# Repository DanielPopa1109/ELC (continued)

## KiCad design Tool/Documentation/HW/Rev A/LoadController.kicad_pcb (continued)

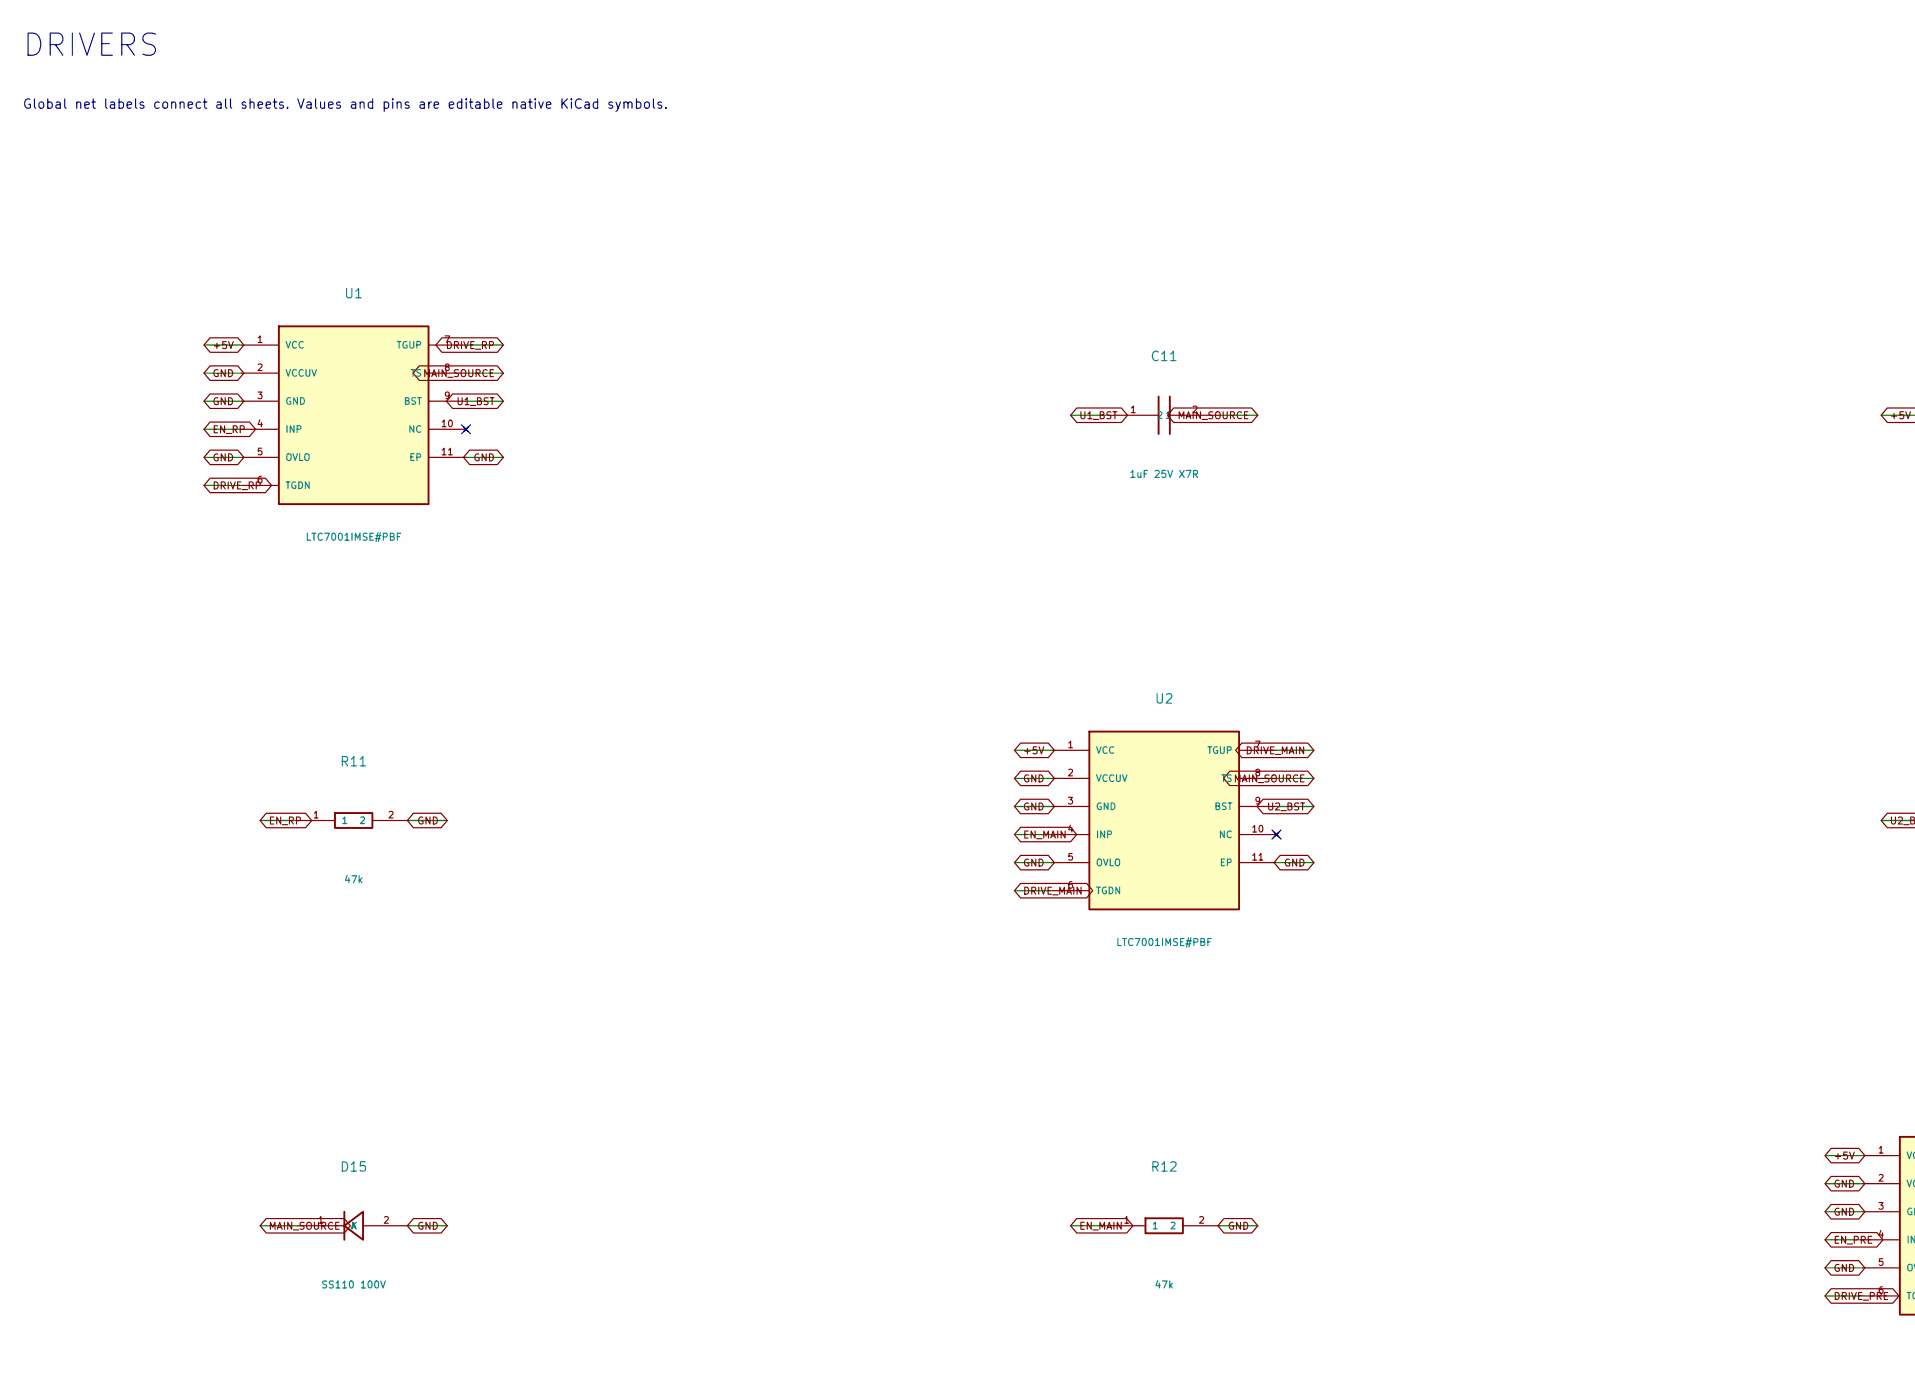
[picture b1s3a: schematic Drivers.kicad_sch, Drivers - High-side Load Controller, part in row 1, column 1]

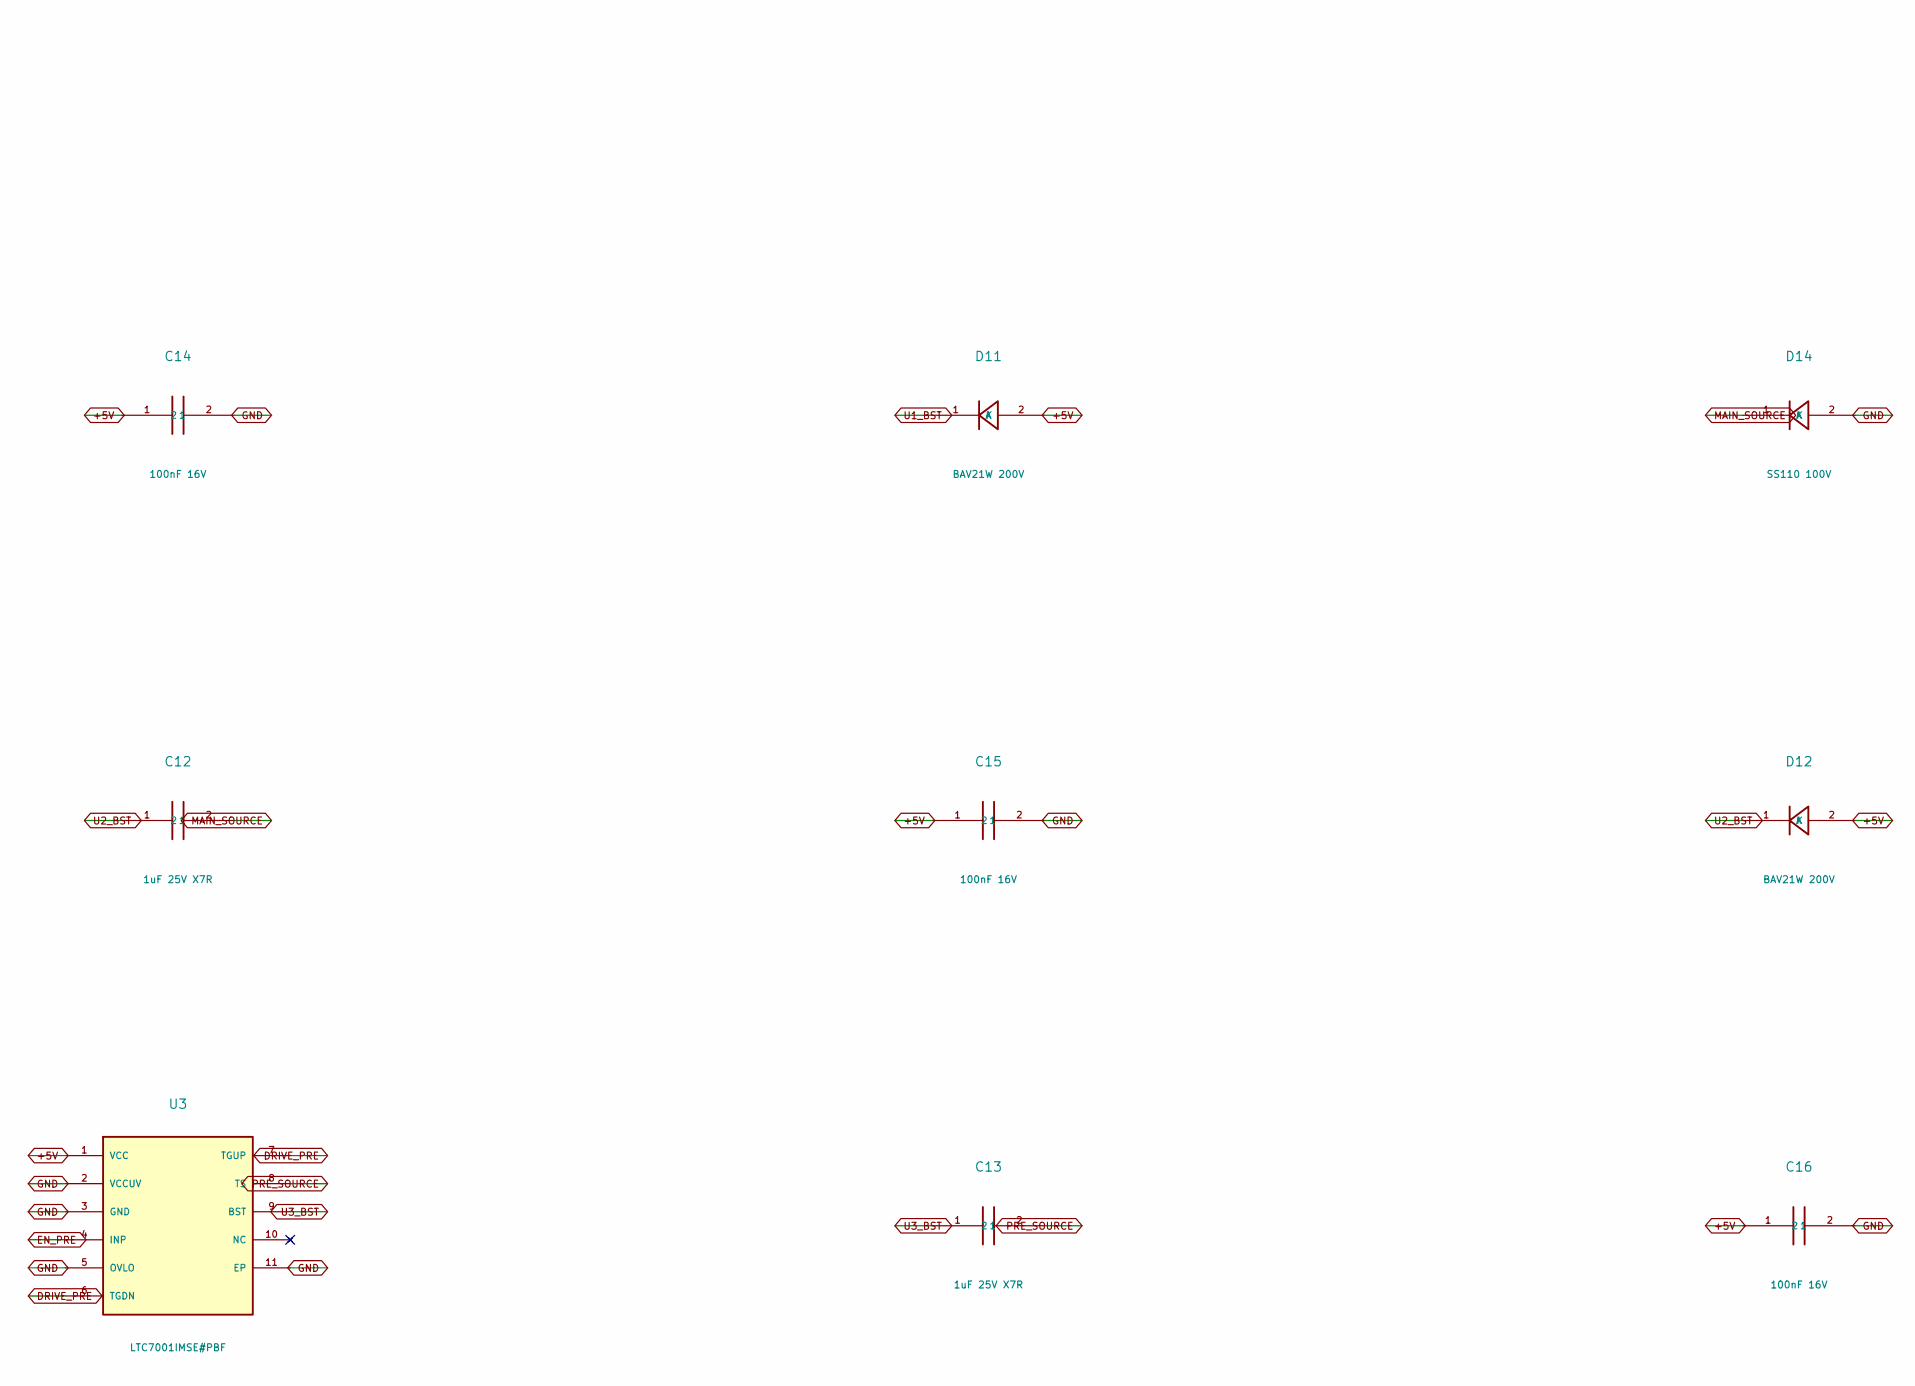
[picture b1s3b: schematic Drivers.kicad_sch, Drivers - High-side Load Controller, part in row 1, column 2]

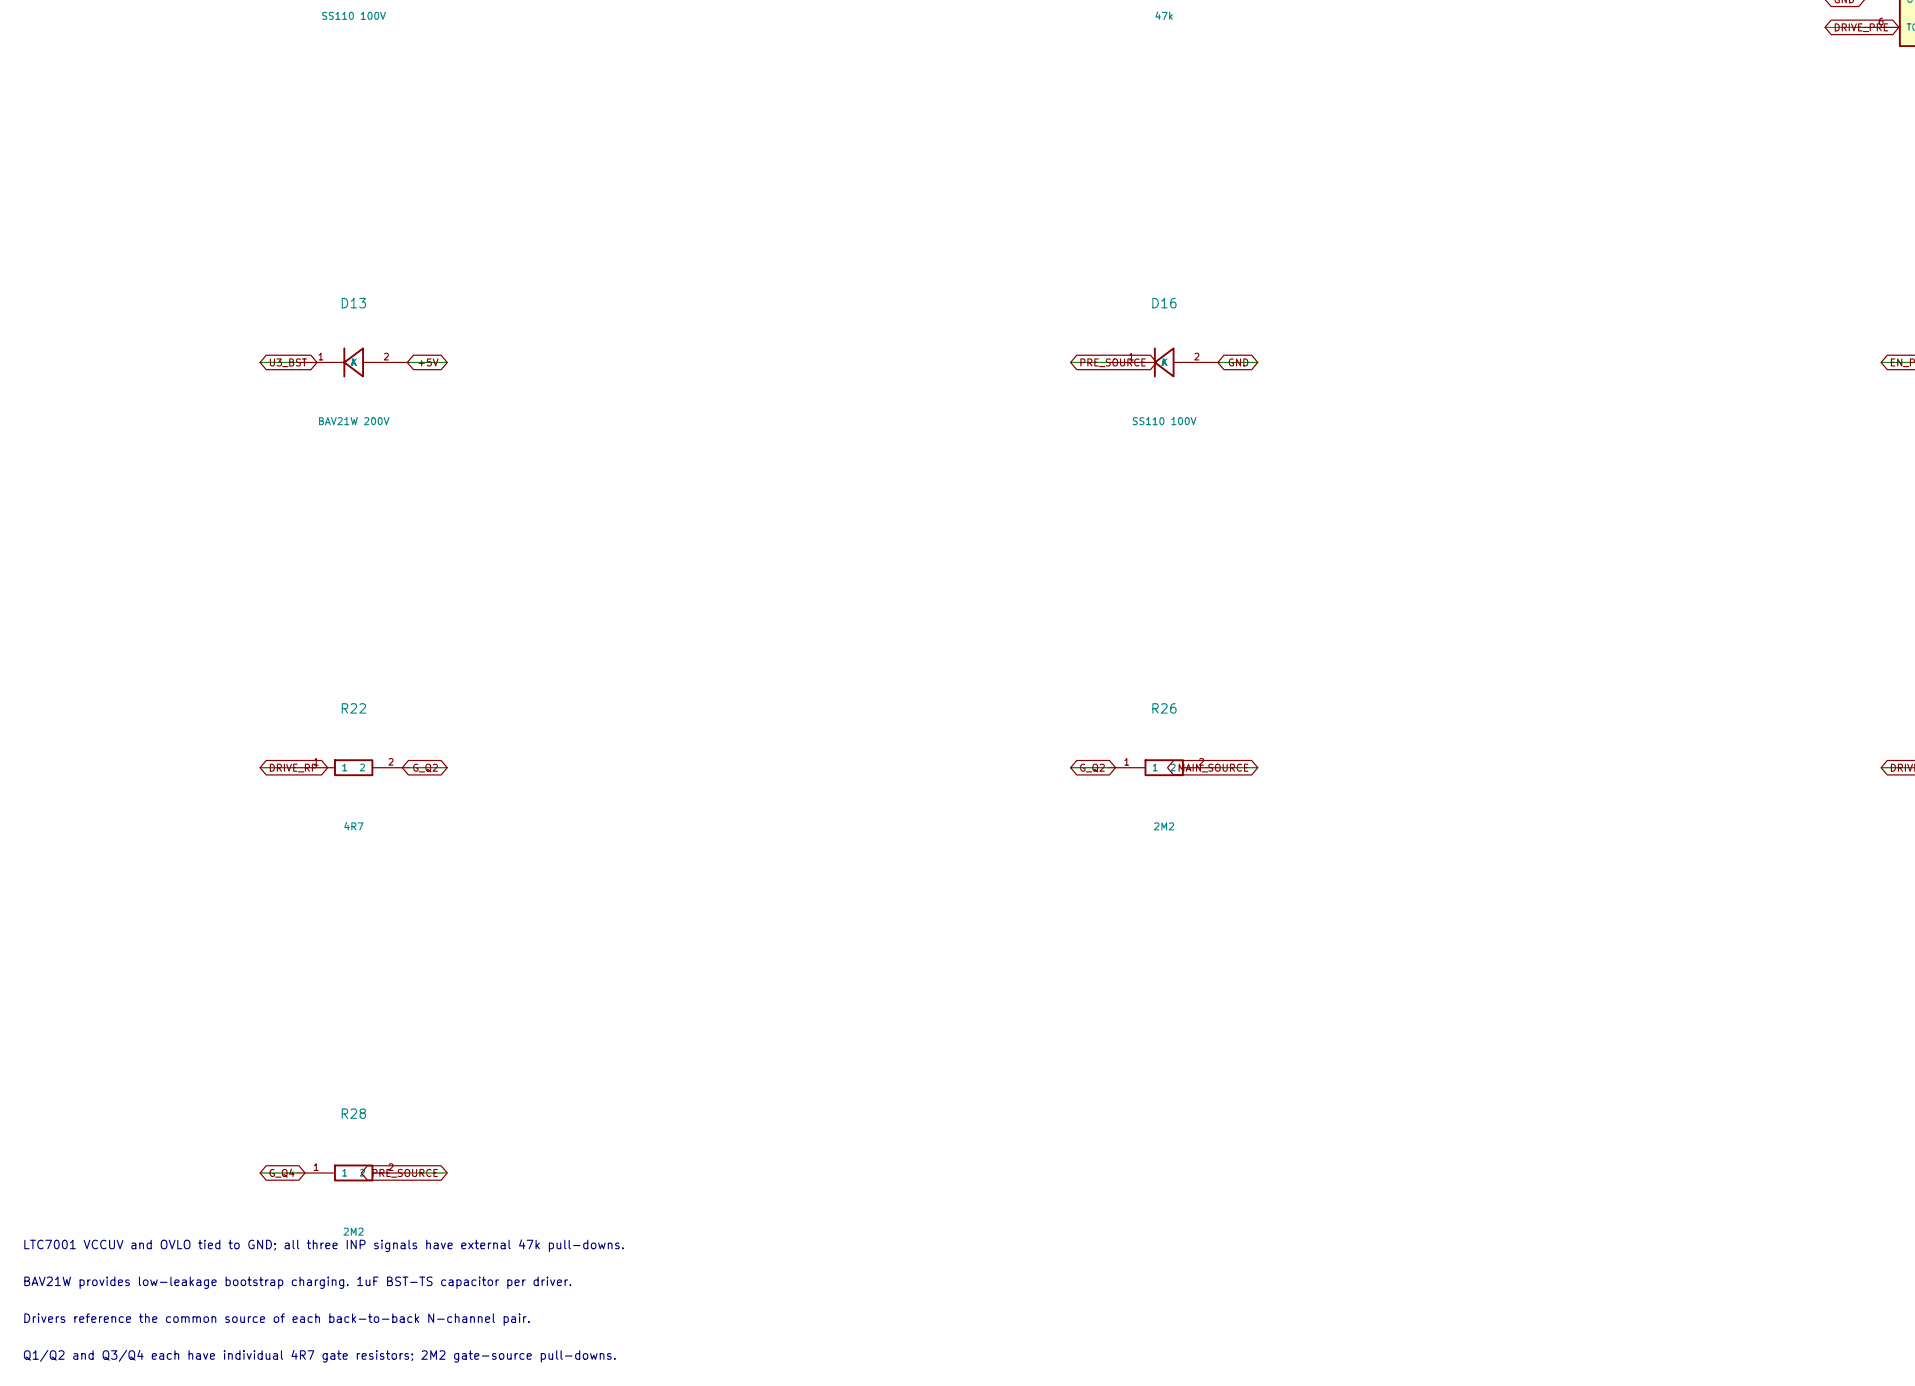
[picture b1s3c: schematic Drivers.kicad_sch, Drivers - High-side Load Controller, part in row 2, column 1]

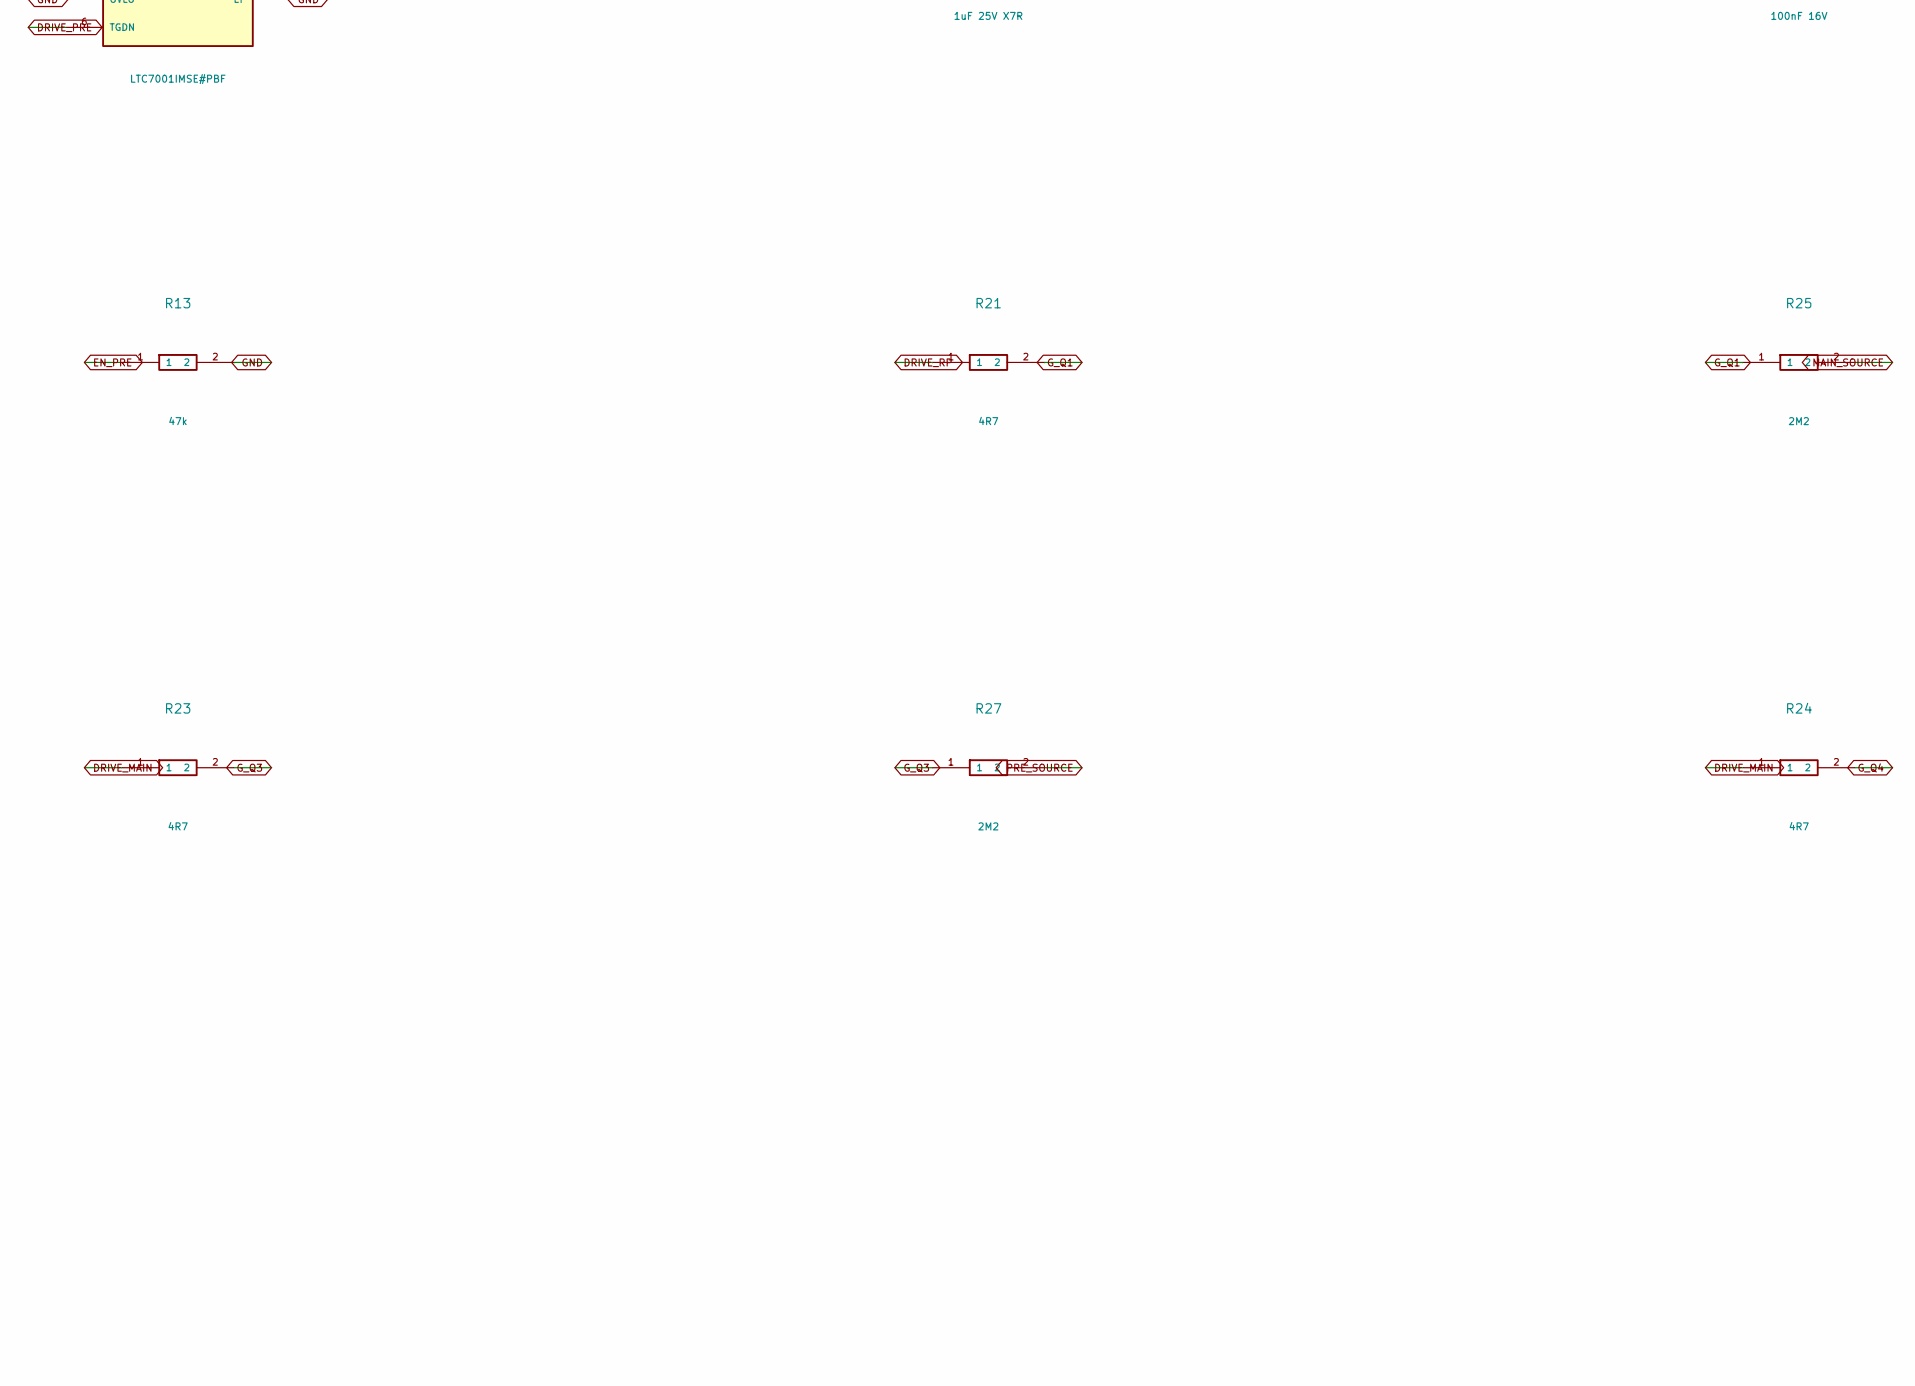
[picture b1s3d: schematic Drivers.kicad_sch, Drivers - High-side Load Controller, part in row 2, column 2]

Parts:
C11, C12, C13: 1uF 25V X7R; 0805
C14, C15, C16: 100nF 16V; 0805
D11, D12, D13: BAV21W 200V; SOD123
D14, D15, D16: SS110 100V; SMA
R11, R12, R13: 47k; 0805
R21, R22, R23, R24: 4R7; 0805
R25, R26, R27, R28: 2M2; 0805
U1, U2, U3: LTC7001IMSE#PBF; MSOP10_EP

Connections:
+5V: C14.1, C15.1, C16.1, D11.2 (A), D12.2 (A), D13.2 (A), U1.1 (VCC), U2.1 (VCC), U3.1 (VCC); also elsewhere on the board
DRIVE_MAIN: R23.1, R24.1, U2.6 (TGDN), U2.7 (TGUP)
DRIVE_PRE: U3.6 (TGDN), U3.7 (TGUP); also elsewhere on the board
DRIVE_RP: R21.1, R22.1, U1.6 (TGDN), U1.7 (TGUP)
EN_MAIN: R12.1, U2.4 (INP); also elsewhere on the board
EN_PRE: R13.1, U3.4 (INP); also elsewhere on the board
EN_RP: R11.1, U1.4 (INP); also elsewhere on the board
GND: C14.2, C15.2, C16.2, D14.2 (A), D15.2 (A), D16.2 (A), R11.2, R12.2, R13.2, U1.2 (VCCUV), U1.3 (GND), U1.5 (OVLO), U1.11 (EP), U2.2 (VCCUV), U2.3 (GND), U2.5 (OVLO), U2.11 (EP), U3.2 (VCCUV), U3.3 (GND), U3.5 (OVLO), U3.11 (EP); also elsewhere on the board
G_Q1: R21.2, R25.1; also elsewhere on the board
G_Q2: R22.2, R26.1; also elsewhere on the board
G_Q3: R23.2, R27.1; also elsewhere on the board
G_Q4: R24.2, R28.1; also elsewhere on the board
U1_BST: C11.1, D11.1 (K), U1.9 (BST)
U2_BST: C12.1, D12.1 (K), U2.9 (BST)
U3_BST: C13.1, D13.1 (K), U3.9 (BST)

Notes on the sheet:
LTC7001 VCCUV and OVLO tied to GND; all three INP signals have external 47k pull-downs.
DRIVERS
Q1/Q2 and Q3/Q4 each have individual 4R7 gate resistors; 2M2 gate-source pull-downs.
Drivers reference the common source of each back-to-back N-channel pair.
Global net labels connect all sheets. Values and pins are editable native KiCad symbols.
BAV21W provides low-leakage bootstrap charging. 1uF BST-TS capacitor per driver.
